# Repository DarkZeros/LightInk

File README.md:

#  LightInk project

E-Ink ESP32 powered Watch that can run solely on solar power!

## What is it?

The main porpose of LightInk project is to have a functional and basic E-Ink watch that can be powered via Solar cell entirely. The power consumption is around 2uA just updating time, therefore a 200mAh battery like "Watchy" has can last around 400 days! (or powered by a small solar cell)

The project is based around the "Watchy" idea, but requires specific HW to reach these low power levels. Basically differs in:
* Has a better TPS63900 power source of 2.6/2.9V
  * More efficient (DC-DC 75nA quiscent, 1A, 1.8-5V regulation, which 2 configurable voltages)
  * This is enough to power ESP32/RTC/Eink and WiFi under all conditions
* Does not have accelerometer (too much power!, even disabled, uses 1uA)
* Does not have solar cell regulation, is connected directly to batery
* Piezo speaker support
* LED light to see display in dark
* Capacitive touch instead of buttons
* Support for LORA/GPS, but yes, they use too much power! (only turn on to send a signal)

## More info

Hackaday.io project page: https://hackaday.io/project/205564-lightink

Youtube channel: https://www.youtube.com/channel/UC85IYb1iQYl5axvtkAJRysg

Videos: 
[![Demo solar video]](https://youtu.be/erjeWSajqhQ?si=WS1v5kafEWmZIDvW)
[![Demo features video]](https://youtu.be/qBj7sOVVzNI?si=8qa2g7JaOwrqm9AO)

Other links: https://www.hackster.io/news/the-lightink-watch-pairs-a-solar-panel-with-epaper-to-deliver-theoretically-infinite-battery-life-ac8c0fdec287

## What is done already ?

The project goals are:
- [X] Ultra low consumption <0.5 mAh/day!
  - [X] Custom Display Driver, reduce booster times/ LUT, etc..
  - [X] Implement a uSPI and display update from wake sleep stub (<1ms! ESP32 on time)
- [X] Basic UI functionality and Widgets
- [X] Features
  - [X] LED light
  - [X] Vibration
  - [X] Speaker
  - [X] GPS
  - [X] Lora receive, BPSK send signals
- [X] Time accurate
  - [X] Manual calibrate drift and adjust it
  - [X] 1ppm Target (now 10ppm)
  - [X] NTP sync - Wifi - AutoZone
- [X] Battery Power support
  - [ ] Track battery & estimate in ULP
  - [X] Auto power save
  - [X] Night time, saving ours
- [X] Touch Settings
  - [X] Capacitive Touch functionality
  - [X] Touch configuration - Sensitivity
- [ ] Watchface configuration
  - [ ] Refactor watchface to be modular with uSPI update
  - [X] Moon Indicator
  - [X] SunSet Sunrise
  - [ ] Tides
  - [ ] Pictures, etc
- [ ] Configurable Alarms
- [ ] BT - Companion App ([android/](android/README.md), [protocol](docs/ble_protocol.md))
  - [X] Pairing and settings sync
  - [ ] LoRa messages through the phone
- [ ] Support other boards
  - [ ] Watchy v1.0 -> [Watchy 1.0 Branch](https://github.com/DarkZeros/LightInk/tree/watchy_1.0)

## The purpose of this project

Have fun optimizing the hell out of this ESP32 to make it low power enough for a solar cell.
This all started as a challenge, that luckily it is starting to look like a real thing after many years.

My plan is to continue developing and adding features/fixes for my personal unit use.
I doubt it will become a comercial product since building a unit requires a lot of soldering.
However I am happy if someone can change my mind on how to mass produce it easily. :)

## Repo structure

```
lightink/
├── firmware/
│   ├── main/         # The LightInk firmware code
│   ├── components/   # Other components & subprojects used in the builds
│   └── esp-idf/      # The ESP-IDF version used to build (it has changes compared to upstream)
│   ...               # Other misc files like partitions / sdkconfig / ...
│
├── android/          # The companion app (pairing and settings over Bluetooth)
│
├── hardware/
│   ├── pcb/          # Schematics, BOM and diagrams
│   └── case/         # STL files for from and back
│
├── docs/
│   ├── images/       # images of the project
│   ...               # Hisotory and important docs
│
├── README.md
└── LICENSE
```
## More info

- 📖 [History](docs/HISTORY.md)
- 🛠️ [Hardware](hardware/HARDWARE.md)
- ✨ [Hardware - Case](hardware/case/CASE.md)
- ⚡ [Hardware - PCB](hardware/pcb/PCB.md)
- 📱 [Companion app](android/README.md)
- 📡 [Bluetooth protocol](docs/ble_protocol.md)

## How to build the firmware?

It should be quite straightforward:
Just clone every submodule, use `setup.sh` and then `idf.py` to build:
```
git submodule update --init --recursive
cd firmware && ./setup.sh && idf.py build flash monitor
```

The first build creates `firmware/main/secrets.cpp` from `secrets.default.cpp`.
Put your WiFi networks and radio signals there: the file is ignored by git, so they
stay on your computer.

## Helping the project

Just push to a non protected branch and ask for PR.
Any contribution is welcomed.

If you want to build a unit for yourself, or support existing ESP32 HW (like watchy), please feel free to add support.

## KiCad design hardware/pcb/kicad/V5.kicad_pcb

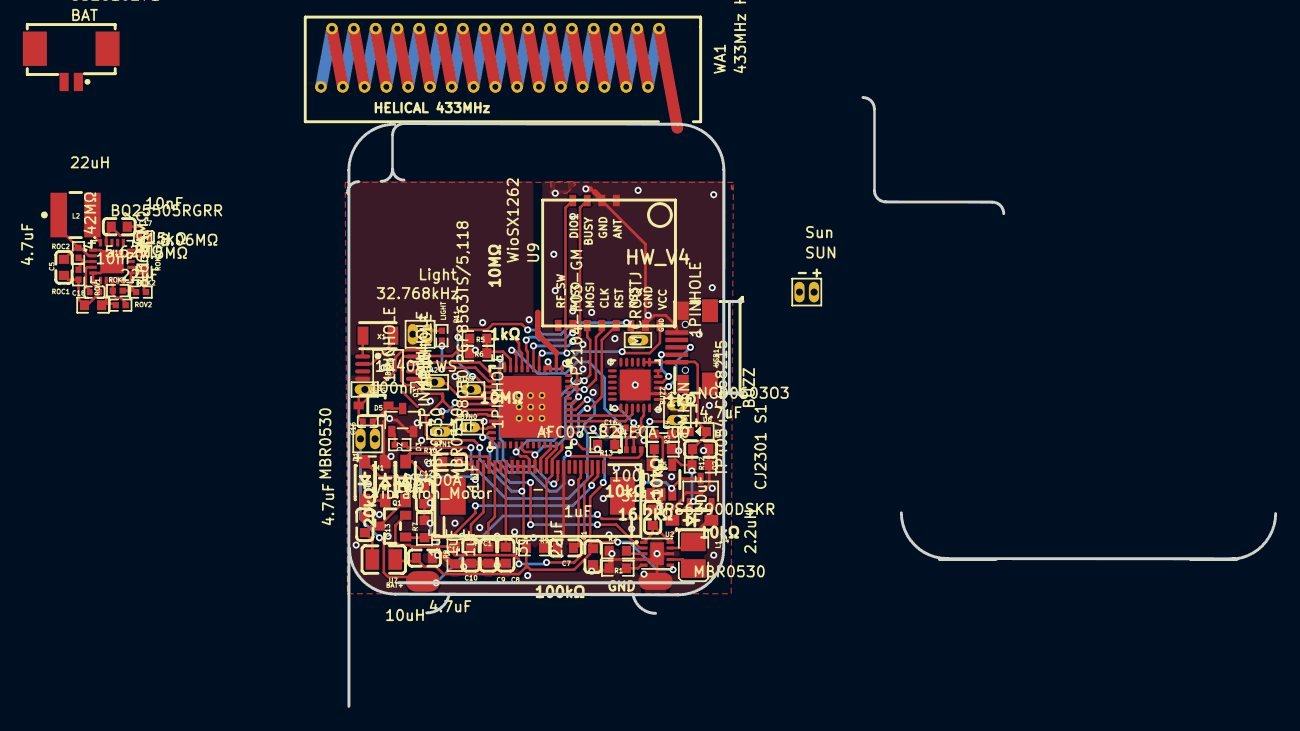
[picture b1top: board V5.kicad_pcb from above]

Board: 2 copper layers, 81.1 x 53.2 mm, 75 parts (1 on the bottom side), 68 nets.

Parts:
+BAT: 1PINHOLE
AE1: SWRA117D
BAT: 532610271; CONN-SMD_532610271
BTN0, BTN1, BTN2, BTN3: 1PINHOLE
BUZZ: BUZZ; VIBRATING-MOTOR-SMD_WELDING
C1, C17: 22uF; C0603
C2: 10uF; C0603
C5, C6, C13, C14: 4.7uF; C0603
C7, C8, C9, C10, C11, C12: 1uF; C0603
C15, C16: 100nF; C0402
C18, C19: 10nF; C0402
D1, D2, D3, D4: MBR0530; SOD-123_L2.7-W1.6-LS3.7-RD-1
D5: 1N4001WS; SOD-323_L1.6-W1.3-LS2.7-RD
FPC1: AFC07-S24ECA-00; FPC-SMD_AFC07-S24ECA-00
GND: 1PINHOLE
L1: 2.2uH; L1008
L2: 22uH; IND-SMD_L3.9-W3.9-1
LIGHT: Light; VIBRATING-MOTOR-SMD_WELDING
M1: Vibration_Motor; VIBRATING-MOTOR-SMD_WELDING
Pad_gge46144: Pad_gge46144
Pad_gge46189: Pad_gge46189
Q1: AO3400A; SOT-23_L2.9-W1.3-P1.90-LS2.4-BR
Q2: CJ2301 S1; SOT-23-3_L3.0-W1.7-P0.95-LS2.9-BR
Q3: S8050; SOT-23-3_L2.9-W1.3-P1.90-LS2.4-BR
Q4: UMH3N; SC-70-6_L2.2-W1.3-P0.65-LS2.1-BR
R1: 16.2kΩ; R0603
R2: 511Ω; R0603
R3, R12, R13: 10kΩ; R0603
R4: 1kΩ; R0603
R5, R6: 10MΩ; R0603
R7: 20kΩ; R0603
R8: 3Ω; R0603
R9: 100kΩ; R0603
R10, R11: 1kΩ; R0402
ROC1: 8.66MΩ; R0402
ROC2: 1.54MΩ; R0402
ROK1: 4.42MΩ; R0603
ROK2: 8.06MΩ; R0402
ROK3: 715kΩ; R0402
ROV1: 5.62MΩ; R0603
ROV2: 7.5MΩ; R0402
SUN: Sun; VIBRATING-MOTOR-SMD_WELDING
U2: TPS63900DSKR; WSON-10_L2.5-W2.5-W0.50-TL-EP
U3: -; LGA-48_L7.0-W7.0-P0.50-BL-EP5.4
U4: CP2104-F03-GM; QFN-24_L4.0-W4.0-P0.50-BL-EP2.7
U5: TP4054_C668215; TSOT-23-5_L2.9-W1.6-P0.95-LS2.8-BR
U6: NCD0603O3; LED0603-RD
U7: 10uH; L0806
U8: PCF8563TS/5,118; TSSOP-8_L3.0-W3.0-P0.65-LS4.9-BL
U9: WioSX1262; SEEED_WIO_SX1262_PINS
U10: BQ25505RGRR; VQFN-20_L3.5-W3.5-P0.50-TL-EP
USB1: MICROQTJ; MICRO-USB-SMD_MICROQTJ
WA1: 433MHz Helical Antenna; 433MHZ HELICAL ANTENNA
X1: 32.768kHz; CRYSTAL-SMD_L3.2-W1.5

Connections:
32KHZ: U3.13, U8.7
+3V3: C1.2, C14.2, FPC1.9, FPC1.10, R9.2, R13.2, U2.6, U3.1, U3.3, U3.4, U3.19, U3.37, U3.43, U3.46, U7.1, U8.8, U9.8
+BAT: +BAT.1, BAT.1, C15.1, D5.1, M1.2, Pad_gge46189.2, Q2.3, R5.1, SUN.2, U5.3, U10.18
+SOL: C5.2, L2.1, ROC2.1, U10.2
AE1_1: AE1.1, U3.2
BAT: R5.2, R6.1, U3.10
BTN0: BTN0.1, U3.22
BTN1: BTN1.1, U3.20
BTN2: BTN2.1, U3.17
BTN3: BTN3.1, U3.16
BUSY: FPC1.16, U3.11
BUZZ: BUZZ.2, U3.39
C7_2: C7.2, FPC1.20
C8_2: C8.2, FPC1.7
C9_2: C9.2, FPC1.5
C10_2: C10.2, FPC1.3
C11_2: C11.2, FPC1.1
D1_1: C13.2, D1.1, D2.2
D3_2: C13.1, D3.2, Q1.3, U7.2
D+: U4.3, USB1.3
D-: U4.4, USB1.2
DC: FPC1.14, U3.35
DIO1: U3.5, U9.12
DTR: Q4.2, Q4.4, U4.23
EN: C16.1, Q4.6, R13.1, U3.9
GDR: FPC1.23, Q1.1, R7.1
GH: C12.1, D3.1, FPC1.4
GL: D1.2, FPC1.2
GND: AE1.2, BAT.2, BUZZ.1, C1.1, C2.1, C5.1, C6.2, C7.1, C8.1, C9.1, C10.1, C11.1, C12.2, C14.1, C16.2, C17.1, C18.2, C19.2, D2.1, FPC1.8, FPC1.17, GND.1, LIGHT.1, Pad_gge46144.2, Q3.2, R1.1, R2.1, R3.1, R6.2, R7.2, R8.2, R12.1, ROC1.2, ROK1.2, ROV1.1, SUN.1, U2.4, U2.8, U2.11, U3.21, U3.49, U4.2, U4.25, U5.2, U8.4, U9.7, U9.10, U10.1, U10.5, U10.14, U10.15, U10.21, USB1.5
GPIO0: Q4.3, U3.23
L2_2: L2.2, U10.20
LIGHT: R11.2, U3.14
LIGHT_2: LIGHT.2, R11.1
LORABUSY: U3.6, U9.11
LORACS: U3.15, U9.6
LORARES: U3.38, U9.5
MISO: U3.7, U9.2
MOSI: FPC1.11, U3.28, U9.3
Q3_1: Q3.1, R10.2
Q3_3: C15.2, D5.2, M1.1, Q3.3
R4_2: R4.2, U6.1
RES: FPC1.15, R9.1, U3.36
RESE: FPC1.22, Q1.2, R8.1
RTS: Q4.1, Q4.5, U4.19
RX: U3.40, U4.21
SCK: FPC1.12, U3.29, U9.4
SS: FPC1.13, U3.34
TX: U3.41, U4.20
U2_1: C2.2, D4.1, Q2.2, U2.1, U2.10
U2_3: R2.2, U2.3
U2_5: R1.2, U2.5
U2_7: L1.2, U2.7
U2_9: L1.1, U2.9
U4_5: U4.5, U4.6
U5_1: R4.1, U5.1
U5_5: R3.2, U5.5
U10_3: ROC1.1, ROC2.2, U10.3
U10_4: C18.1, U10.4
U10_7: ROV1.2, ROV2.1, U10.7
U10_8: ROK3.1, ROV2.2, U10.8
U10_11: ROK2.1, ROK3.2, U10.11
U10_12: ROK1.1, ROK2.2, U10.12
U10_19: C17.2, C19.1, U10.19
VBUS: C6.1, D4.2, Q2.1, R12.2, U4.7, U4.8, U5.4, U6.2, USB1.1
VIB: R10.1, U3.42
VSEL: U2.2, U3.24
XN: U8.2, X1.2
XP: U8.1, X1.1

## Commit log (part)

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2026-03-01 Updated IDF 5.5.1 + Arduino 3.3.5
    - 911kB (Arduino 3.3 + IDF 5.5)
    - 934kB (Arduino 3.3.5 + IDF 5.5)
    - 938kB (Arduino 3.3.5 + IDF 5.5.1)
2026-03-01 Touch fixes for phantom touch
    * Fixed by setting the touch after touch events
    This allows enough time for events to settle
    * Enable touch trigger at the end, avoids issues
    * Also cache the touch mode to avoid resetting
2026-03-01 Auto turn off GPS
    * Set to 60s, and update every 10s
2026-03-01 fixup NTP sync
2026-03-01 DRAFT
2026-03-01 Allow to disable LowVoltage
    * Display has slightly less quality
    using low voltage
2026-03-01 Track display changes
2026-03-01 Watchface rework WIP
2026-04-12 Rework the DateTime menu
    * Allow to underflow properly
    * Propagate the change back to other values
    ie: 01h00m00s -1s = 00h59m59s
2026-04-12 Fixing Speaker resets
2026-04-12 Wifi multiAP and NTP fixes
    * Allow multiAP wifi secrets
    * NTP gets location as well for setting sun without GPS
2026-04-12 Use new Adafruit Elipse
    * Slightly slower (10%) but more reliable
    * Refactor drawMoonFast and make it work (430us -> 280us)!
2026-04-12 More display optimizations
    * Replace /% with >> and &
2026-04-12 Found out quality in display issue
    * Culprit is Booster time adjustments
    Need to pinpoint power usage and benefits...
    * Maybe create an option, low quality high quality...
    * TODO meadure costs!!
2026-04-16 Fixup secrets default
2026-04-16 Fix sdkconfig required for Wifi/BT
2026-04-16 Fixup fast moon
2026-04-19 WIP display refactor
2026-04-19 More cleanups
2026-04-19 Play with RTC display buffer
2026-04-19 TRACE added WIP
2026-04-19 WIP Fixed rendering on the new code
    * Still not stable
2026-04-27 WIP Compression
2026-04-29 WIP ADC Bat
2026-05-02 Refactor uSPI
    * Separate to cpp to be usable in multiple places
    * Fix minor things in display code to point to
    single SPI unit, thn allow to be uSPI or SPI.
2026-05-02 Final readme and logos
2026-05-05 Create LICENSE GPL v3
    Add a licence GPLv3 since this project is not a library.
    I would like it to be open, but also people to contribute
    and not just some company to steal the code and build a commercial product (at least not without collaboration)
2026-05-10 Optimize uSPI transfer
    * Reduced the typical case -4% the time
    *
2026-05-11 History-Case-HW-PCB
2026-05-14 Fix timezone setting
    * Simplified the code and removed old NTP code
    The new one works better.
    * Use less network as well, by reducing the parameters
    * Reduced size by 45kB !
2026-05-20 Fix GPS staying on
2026-05-20 Minor fixes
2026-05-20 Partial support watchy v1.0
    * NOTE: Requires a Different sdkconfig file to renable the 150kHz
    * Renamed Touch to Input
    * Refactor Input to 2 clases / Buttons and Touch
    * Refactor Hardware classes
2026-05-20 Watchy v1.0 SDKconfig
    * Need to make this being picked up automatically
2026-05-22 WIP BLE companion APP
2026-05-22 Move the secrets file!
